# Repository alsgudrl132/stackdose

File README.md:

# stackdose

**버튼 한 번으로 내 보충제 조합(스택) 1회분을 컵에 담아 주는 디스펜서**

가루 4종과 알약·캡슐 4종을 넣어 두고, 웹에서 "운동 전", "운동 후" 같은 프리셋을 누르면 정해 둔 양만큼 담아 줍니다. 컵은 두 개로, 가루 컵은 가루 스테이션 저울 위에, 알약 컵은 알약 스테이션에 놓습니다. 가루는 저울로 무게를 재면서 목표량이 되면 멈추고, 알약은 원판이 돌면서 한 알씩 떨어뜨립니다.

> **진행 상황 (2026-09):** 3D 설계와 배선 설계를 마쳤고, 부품을 주문하는 단계입니다. 아직 실물로 만들어 보지 않았습니다. 다음은 웹(백엔드 + 가상 디스펜서)입니다.

## 기능

- **프리셋 3개 이상:** 사용자 설정 1·2·3…마다 가루 몇 g, 알약 몇 알을 저장
- **가루 4칸:** 스크류(오거)가 가루를 밀어내고, 컵 밑 로드셀로 무게를 보면서 목표 g에서 멈춤 (폐루프)
- **알약 4칸:** 칸이 3개인 원판이 120°씩 돌아 한 알씩 배출. 자석 + 홀 센서로 원점을 찾음
- **웹 먼저:** 하드웨어가 없어도 가상 디스펜서로 전체 흐름을 돌려 볼 수 있게 만들 예정

## 구조

| 가루 모듈 | 알약 모듈 |
|---|---|
|  |  |
| JGA25-370 DC 모터 + 3D 프린트 스크류. 네 모듈이 컵 위에서 X자로 모임 | 28BYJ-48 스텝 모터 + 칸 3개 원판. 출구 아래 미끄럼관이 컵으로 이어짐 |

```
웹 (프리셋 선택) ──HTTP──▶ ESP32 ─┬─ DRV8833 ×2 ── 가루 모터 ×4
                                 ├─ MCP23017 (I2C) ── ULN2003 ×4 ── 알약 모터 ×4
                                 ├─ HX711 ── 로드셀 1kg (컵 무게)
                                 └─ 홀 센서 ×4 (알약 원판 원점)
```

## 폴더

| 폴더 | 내용 |
|---|---|
| [hardware/cad](hardware/cad) | OpenSCAD 설계 (치수는 `config.scad` 한 곳), 출력용 STL, 자동 검사 스크립트 |
| [hardware/wiring.md](hardware/wiring.md) | 전원, ESP32 핀 배정, 선 길이 |
| [hardware/parts.md](hardware/parts.md) | 부품표 |
| `backend/` · `frontend/` · `firmware/` | 예정 |

## 설계 원칙

- **서포트 없이 출력:** 모든 부품이 Ender-3 SE(220×220mm)에 서포트 없이 들어가도록 방향과 모양을 잡았습니다.
- **나사 20개:** 힘을 받는 곳(모터, 로드셀)에만 나사를 쓰고, 나머지는 핀·돌기·턱으로 끼우거나 한 덩어리로 출력합니다.
- **검사하고 출력:** `python hardware/cad/check.py`가 부품 렌더 오류, 출력판 크기, 떨어진 조각, 조립 상태의 부품 겹침(155쌍), 컵을 꺼내는 길, 알약 원판의 대기 위치를 검사합니다. `overhang.py`는 서포트가 필요한 면을 찾습니다.
- **공차는 쿠폰으로:** 프린터마다 다른 끼워 맞춤 여유를 공차 쿠폰 하나로 재서 `config.scad`에 넣습니다.

## 로드맵

- [x] 3D 설계 · 자동 검사
- [x] 배선 설계 · 부품 선정
- [ ] 백엔드: FastAPI + SQLite (프리셋, 배출 기록)
- [ ] 프론트엔드: 프리셋 화면 + 가상 디스펜서
- [ ] 펌웨어: ESP32 (무게 폐루프 배출, 원점 찾기)
- [ ] 출력 · 조립 · 실측값 반영

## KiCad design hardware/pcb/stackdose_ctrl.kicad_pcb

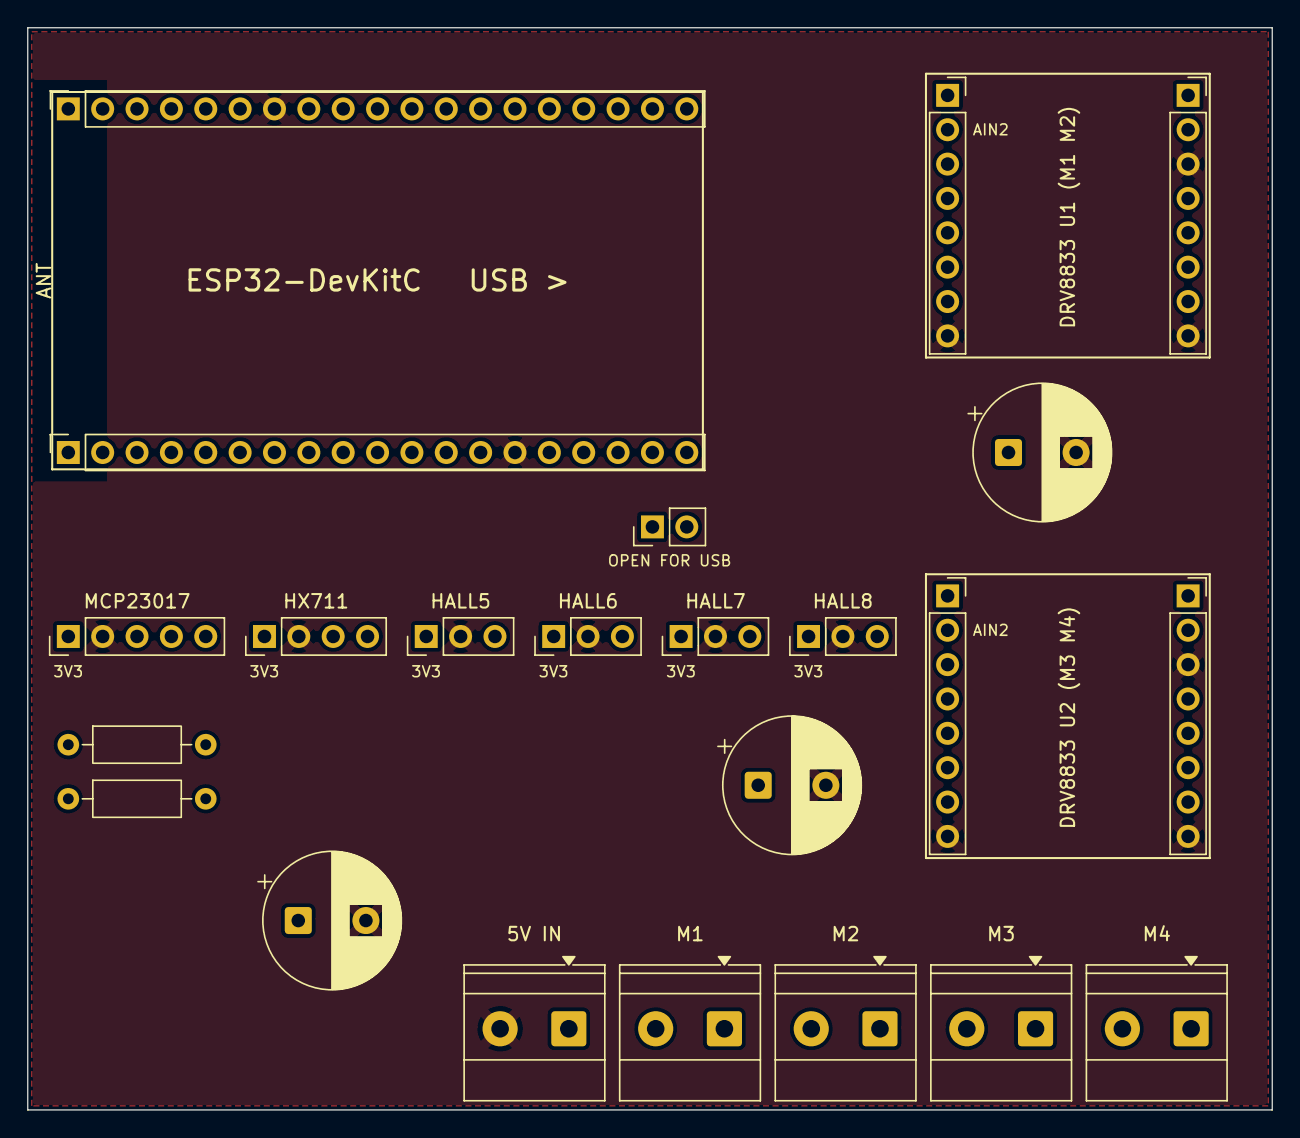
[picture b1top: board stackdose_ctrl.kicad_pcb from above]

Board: 2 copper layers, 92.0 x 80.0 mm, 23 parts (0 on the bottom side), 28 nets, no tracks yet.

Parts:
C1, C2, C3: 1000uF 10V; CP_Radial_D10.0mm_P5.00mm
J1: ESP32 top; PinSocket_1x19_P2.54mm_Vertical
J2: ESP32 bottom; PinSocket_1x19_P2.54mm_Vertical
J3, J5: DRV8833 L; PinSocket_1x08_P2.54mm_Vertical
J4, J6: DRV8833 R; PinSocket_1x08_P2.54mm_Vertical
J7: MCP23017; PinHeader_1x05_P2.54mm_Vertical
J8: HX711; PinHeader_1x04_P2.54mm_Vertical
J9: HALL5; PinHeader_1x03_P2.54mm_Vertical
J10: HALL6; PinHeader_1x03_P2.54mm_Vertical
J11: HALL7; PinHeader_1x03_P2.54mm_Vertical
J12: HALL8; PinHeader_1x03_P2.54mm_Vertical
J13: 5V IN; TerminalBlock_Phoenix_MKDS-1,5-2-5.08_1x02_P5.08mm_Horizont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
J14: M1; TerminalBlock_Phoenix_MKDS-1,5-2-5.08_1x02_P5.08mm_Horizont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
J15: M2; TerminalBlock_Phoenix_MKDS-1,5-2-5.08_1x02_P5.08mm_Horizont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
J16: M3; TerminalBlock_Phoenix_MKDS-1,5-2-5.08_1x02_P5.08mm_Horizont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
J17: M4; TerminalBlock_Phoenix_MKDS-1,5-2-5.08_1x02_P5.08mm_Horizont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
JP1: 5V-ESP; PinHeader_1x02_P2.54mm_Vertical
R1, R2: 4.7k; R_Axial_DIN0207_L6.3mm_D2.5mm_P10.16mm_Horizontal

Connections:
+3V3: J2.1, J3.4, J5.4, J7.1, J8.1, J9.1, J10.1, J11.1, J12.1, R1.2, R2.2
+5V: C1.1, C2.1, C3.1, J4.1, J6.1, J7.5, J13.1, JP1.1
ESP_5V: J2.19, JP1.2
GND: C1.2, C2.2, C3.2, J1.1, J1.7, J2.14, J3.8, J4.3, J4.8, J5.8, J6.3, J6.8, J7.2, J8.2, J9.2, J10.2, J11.2, J12.2, J13.2
HALL1: J2.3, J9.3
HALL2: J2.4, J10.3
HALL3: J2.5, J11.3
HALL4: J2.6, J12.3
HX_DT: J1.9, J8.3
HX_SCK: J2.8, J8.4
M1_IN1: J2.9, J3.3
M1_IN2: J2.10, J3.2
M1_OUT1: J4.4, J14.1
M1_OUT2: J4.5, J14.2
M2_IN1: J2.11, J3.5
M2_IN2: J2.15, J3.6
M2_OUT1: J4.7, J15.1
M2_OUT2: J4.6, J15.2
M3_IN1: J2.7, J5.3
M3_IN2: J1.2, J5.2
M3_OUT1: J6.4, J16.1
M3_OUT2: J6.5, J16.2
M4_IN1: J1.13, J5.5
M4_IN2: J1.8, J5.6
M4_OUT1: J6.7, J17.1
M4_OUT2: J6.6, J17.2
SCL: J1.3, J7.4, R2.1
SDA: J1.6, J7.3, R1.1
